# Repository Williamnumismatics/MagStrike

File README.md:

# MagStrike

MagStrike is a custom hall effect keyboard that has a 60 percent layout.
It uses the Gateron Low Profile Magnetic Jade Switches. The brains of this keyboard is a Rpi Pico 2 that runs micropython that communicates with a python script running on the main PC/Laptop

## Why did i build this???
I built this keyboard because i have always wanted to make my own keyboard from scratch and when i stumbled across hall-effect one day i quickly fell in love with it. I also wanted to use low profile switches so my wrists wouldnt hurt all day. I Found the perfect switch for this which is the Gateron Low Profile Magnetic Jade switches.

## What did it take?
It took about 2 weeks to build this it is my first every PCB and unfortunately i couldn't find anywhere to place the rasberry pi pico so i had to put it outside the keyboard. I also designed the case without a top plate so it is easy to print and easy to see the insides

## If i did it again what would i do?
 I would probably make a custom devboard with the rp2040 and embed it inside the footprint of the keyboard.
 
## READ THIS:
the 3d file was to big to commit to github so this is the google drive link:
    https://drive.google.com/file/d/1xGtgr9WMyzFMHPNl8FSLAcrnGV7yFdcr/view
 
### My Bill of Materials

| Item | Description | Quantity | Unit Price (USD) | Total Price (USD) | Shipping(USD) | URL | Running Total(USD) |
| :--- | :--- | :--- | :--- | :--- | :--- | :--- | :--- |
| Switches | Gateron Low Profile Magnetic Jade | 1 x pack of 70 | 56 | 56 | 4.3 | [Link](https://www.gateron.com/products/gateron-low-profile-magnetic-jade-switch?VariantsId=10872) | 60.3 |
| Stabilizer | GATERON Low Profile Plate Mounted Stabilizer | 1 | 8 | 8 | 2.45(Processing Fee) | [Link](https://www.gateron.com/products/gateron-low-profile-plate-mounted-stabilizer?VariantsId=10540) | 70.75 |
| Capacitor | 50V 100nF X7R ±10% 0603 Ceramic Capacitors RoHS | 100 | 0.0025 | 0.25 | 8.87 | [Link](https://www.lcsc.com/product-detail/C14663.html?utm_source=chatgpt.com) | 79.87 |
| Hall Effect Sensor | Analog-Bipolar Hall Effect Sensor | 70 | 0.2345 | 16.42 | N/A | [Link](https://www.lcsc.com/product-detail/C962159.html) | 96.29 |
| Multiplexer | IC MUX 16:1 160OHM 24SOIC | 5 | 0.83 | 3.32 | N/A | [Link](https://www.lcsc.com/sea rch?q=%20CD74HC4067M96%20&s_z=n_%20CD74HC4067M96%20) | 99.61 |
| Rasberry Pi Pico | Rasberry Pi Pico | 1 | 4.32 | 4.32 | 2.42 | [Link](https://core-electronics.com.au/raspberry-pi-pico.html) | 106.35 |
| PCB | THE pcb | 5 | N/A | 26.35 | 18.43 | [Link](https://cart.jlcpcb.com/shopcart/cart/) | 151.13 |

### I didnt include all of the shopping carts so here it is(Note that on gateron website it says some cheaper that the bom but that is cause of a sale that is ending in 16 hours.):

# 3d render:

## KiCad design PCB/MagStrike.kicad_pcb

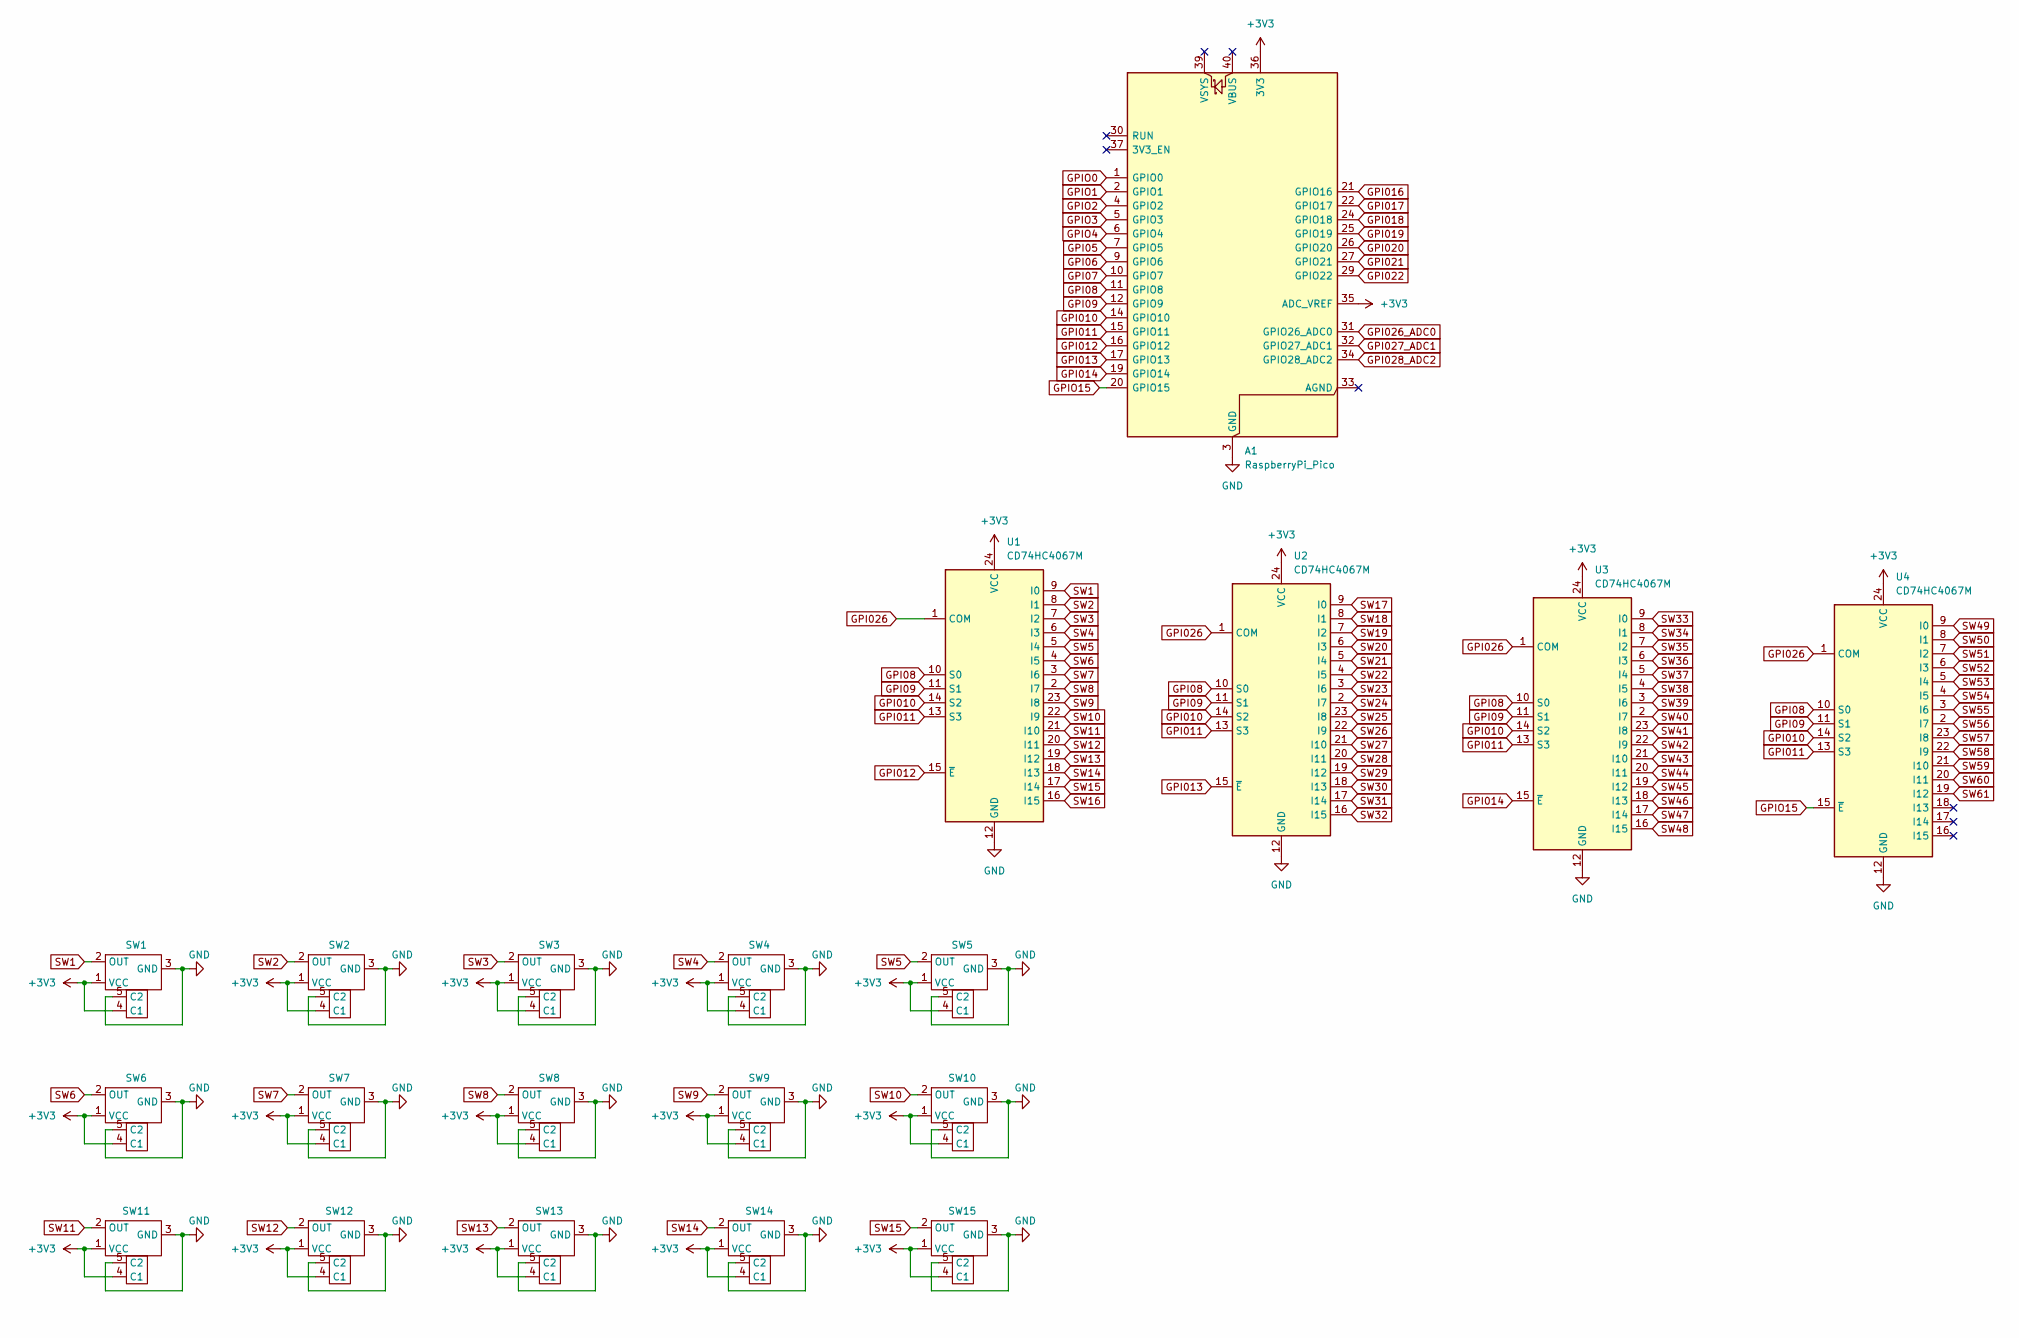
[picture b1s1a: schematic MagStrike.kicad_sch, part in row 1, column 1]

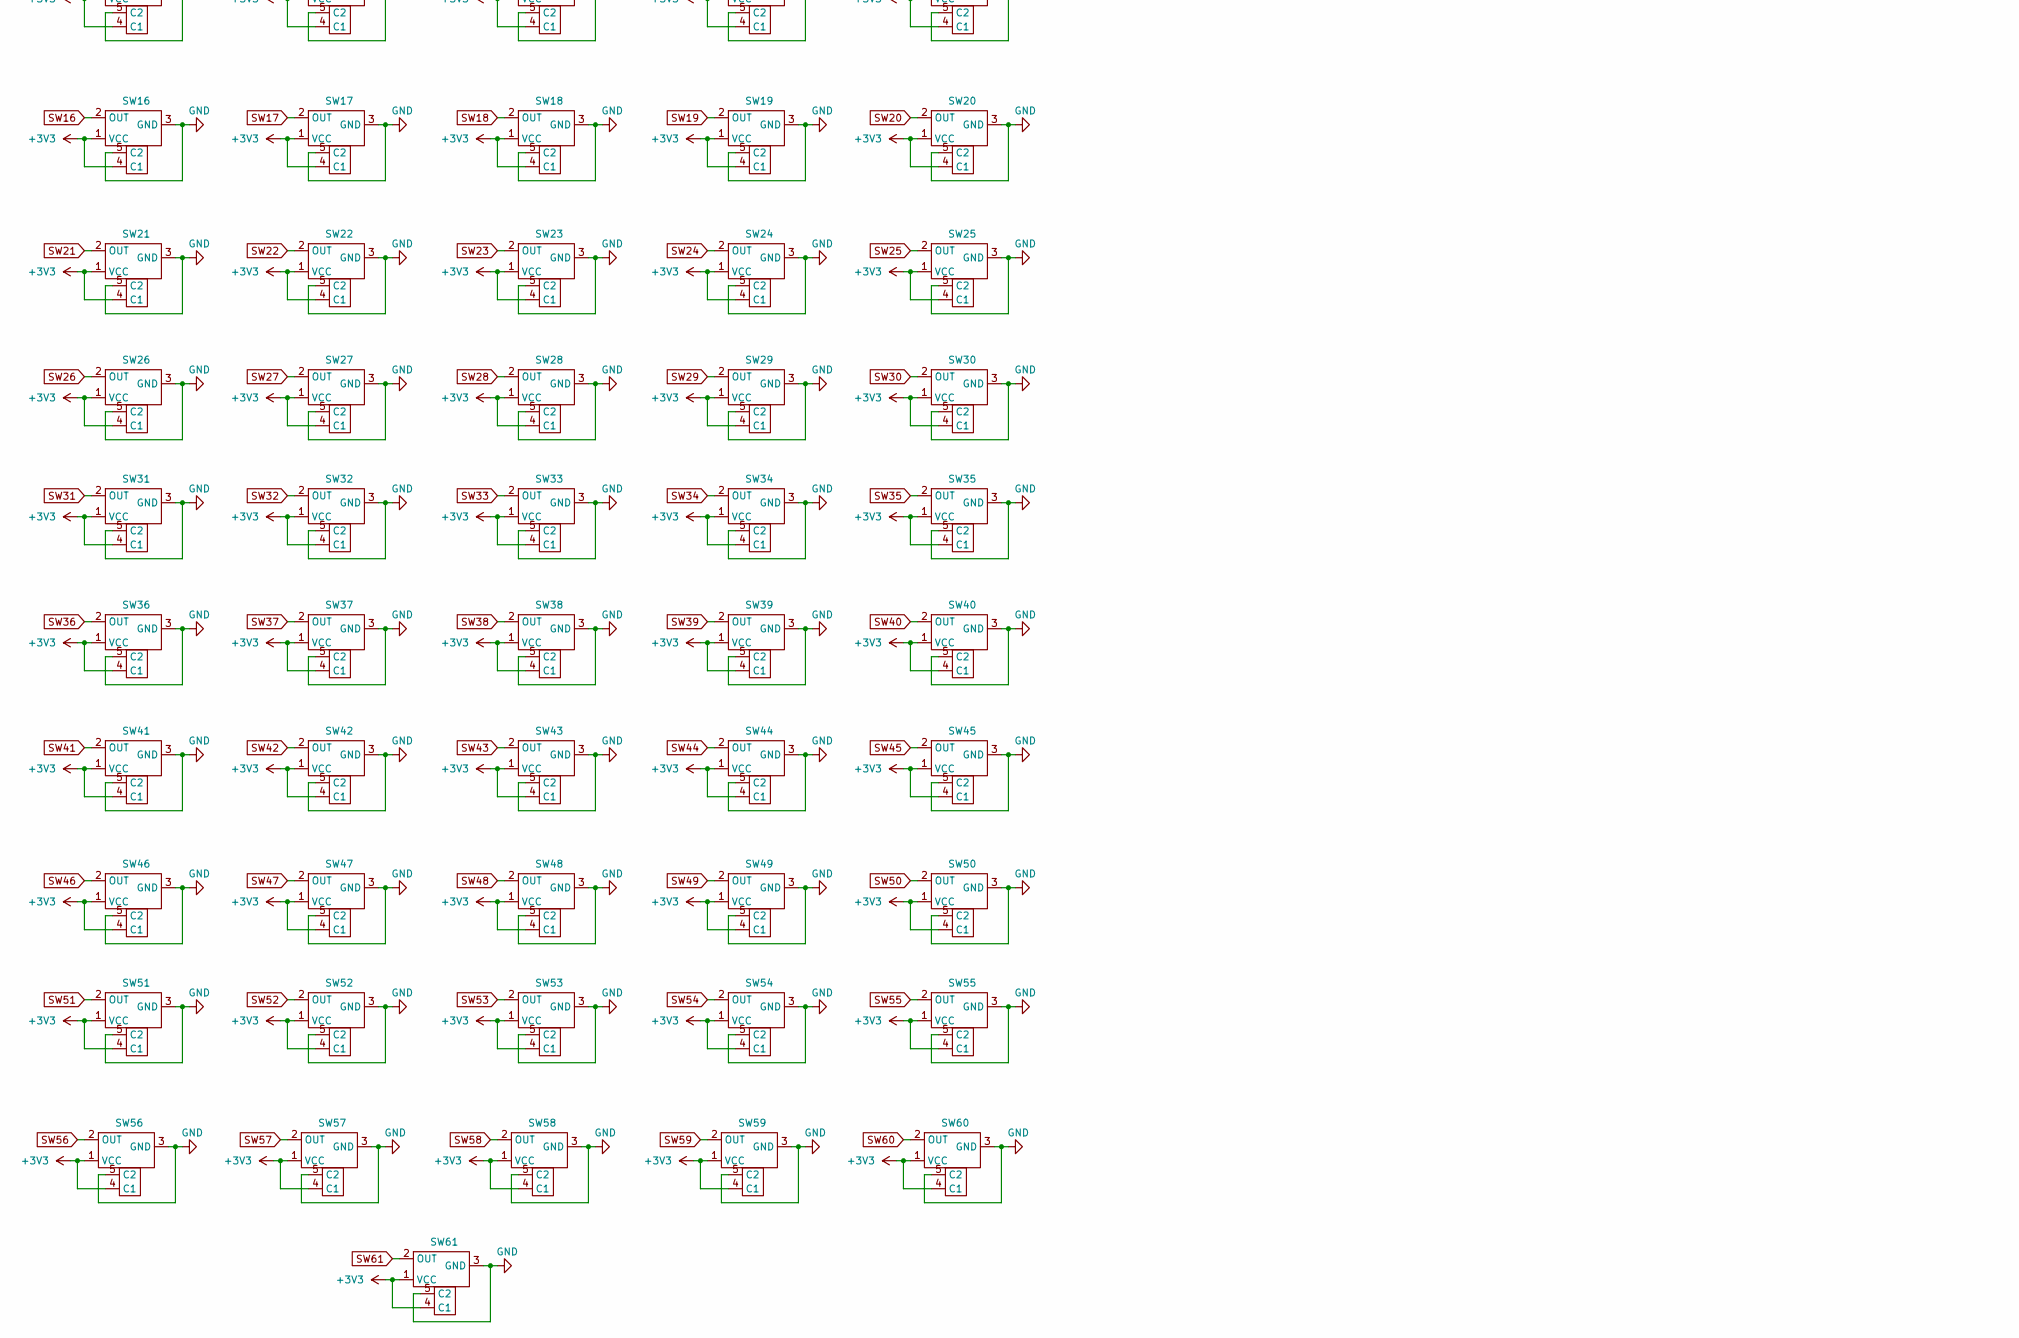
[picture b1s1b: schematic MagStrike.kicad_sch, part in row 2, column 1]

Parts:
A1: RaspberryPi_Pico; RaspberryPi_Pico_Common_Unspecified
SW1, SW2, SW3, SW4, SW5, SW6, SW7, SW8, SW9, SW10, SW11, SW12, SW13, SW14, SW15, SW16, SW17, SW18, SW19, SW20, SW21, SW22, SW23, SW24, SW25, SW26, SW27, SW28, SW29, SW30, SW31, SW32, SW33, SW34, SW35, SW36, SW37, SW38, SW39, SW40, SW41, SW42, SW43, SW44, SW45, SW46, SW47, SW48, SW49, SW50, SW51, SW52, SW53, SW54, SW55, SW56, SW57, SW58, SW59, SW60, SW61: Gateron_Low_Profile_Magnetic_Jade
U1, U2, U3, U4: CD74HC4067M; SOIC-24W_7.5x15.4mm_P1.27mm

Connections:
+3V3: A1.35 (ADC_VREF), A1.36 (3V3), SW1.1 (VCC), SW1.4 (C1), SW2.1 (VCC), SW2.4 (C1), SW3.1 (VCC), SW3.4 (C1), SW4.1 (VCC), SW4.4 (C1), SW5.1 (VCC), SW5.4 (C1), SW6.1 (VCC), SW6.4 (C1), SW7.1 (VCC), SW7.4 (C1), SW8.1 (VCC), SW8.4 (C1), SW9.1 (VCC), SW9.4 (C1), SW10.1 (VCC), SW10.4 (C1), SW11.1 (VCC), SW11.4 (C1), SW12.1 (VCC), SW12.4 (C1), SW13.1 (VCC), SW13.4 (C1), SW14.1 (VCC), SW14.4 (C1), SW15.1 (VCC), SW15.4 (C1), SW16.1 (VCC), SW16.4 (C1), SW17.1 (VCC), SW17.4 (C1), SW18.1 (VCC), SW18.4 (C1), SW19.1 (VCC), SW19.4 (C1), SW20.1 (VCC), SW20.4 (C1), SW21.1 (VCC), SW21.4 (C1), SW22.1 (VCC), SW22.4 (C1), SW23.1 (VCC), SW23.4 (C1), SW24.1 (VCC), SW24.4 (C1), SW25.1 (VCC), SW25.4 (C1), SW26.1 (VCC), SW26.4 (C1), SW27.1 (VCC), SW27.4 (C1), SW28.1 (VCC), SW28.4 (C1), SW29.1 (VCC), SW29.4 (C1), SW30.1 (VCC), SW30.4 (C1), SW31.1 (VCC), SW31.4 (C1), SW32.1 (VCC), SW32.4 (C1), SW33.1 (VCC), SW33.4 (C1), SW34.1 (VCC), SW34.4 (C1), SW35.1 (VCC), SW35.4 (C1), SW36.1 (VCC), SW36.4 (C1), SW37.1 (VCC), SW37.4 (C1), SW38.1 (VCC), SW38.4 (C1), SW39.1 (VCC), SW39.4 (C1), SW40.1 (VCC), SW40.4 (C1), SW41.1 (VCC), SW41.4 (C1), SW42.1 (VCC), SW42.4 (C1), SW43.1 (VCC), SW43.4 (C1), SW44.1 (VCC), SW44.4 (C1), SW45.1 (VCC), SW45.4 (C1), SW46.1 (VCC), SW46.4 (C1), SW47.1 (VCC), SW47.4 (C1), SW48.1 (VCC), SW48.4 (C1), SW49.1 (VCC), SW49.4 (C1), SW50.1 (VCC), SW50.4 (C1), SW51.1 (VCC), SW51.4 (C1), SW52.1 (VCC), SW52.4 (C1), SW53.1 (VCC), SW53.4 (C1), SW54.1 (VCC), SW54.4 (C1), SW55.1 (VCC), SW55.4 (C1), SW56.1 (VCC), SW56.4 (C1), SW57.1 (VCC), SW57.4 (C1), SW58.1 (VCC), SW58.4 (C1), SW59.1 (VCC), SW59.4 (C1), SW60.1 (VCC), SW60.4 (C1), SW61.1 (VCC), SW61.4 (C1), U1.24 (VCC), U2.24 (VCC), U3.24 (VCC), U4.24 (VCC)
GND: A1.3 (GND), A1.8 (GND), A1.13 (GND), A1.18 (GND), A1.23 (GND), A1.28 (GND), A1.38 (GND), SW1.3 (GND), SW1.5 (C2), SW2.3 (GND), SW2.5 (C2), SW3.3 (GND), SW3.5 (C2), SW4.3 (GND), SW4.5 (C2), SW5.3 (GND), SW5.5 (C2), SW6.3 (GND), SW6.5 (C2), SW7.3 (GND), SW7.5 (C2), SW8.3 (GND), SW8.5 (C2), SW9.3 (GND), SW9.5 (C2), SW10.3 (GND), SW10.5 (C2), SW11.3 (GND), SW11.5 (C2), SW12.3 (GND), SW12.5 (C2), SW13.3 (GND), SW13.5 (C2), SW14.3 (GND), SW14.5 (C2), SW15.3 (GND), SW15.5 (C2), SW16.3 (GND), SW16.5 (C2), SW17.3 (GND), SW17.5 (C2), SW18.3 (GND), SW18.5 (C2), SW19.3 (GND), SW19.5 (C2), SW20.3 (GND), SW20.5 (C2), SW21.3 (GND), SW21.5 (C2), SW22.3 (GND), SW22.5 (C2), SW23.3 (GND), SW23.5 (C2), SW24.3 (GND), SW24.5 (C2), SW25.3 (GND), SW25.5 (C2), SW26.3 (GND), SW26.5 (C2), SW27.3 (GND), SW27.5 (C2), SW28.3 (GND), SW28.5 (C2), SW29.3 (GND), SW29.5 (C2), SW30.3 (GND), SW30.5 (C2), SW31.3 (GND), SW31.5 (C2), SW32.3 (GND), SW32.5 (C2), SW33.3 (GND), SW33.5 (C2), SW34.3 (GND), SW34.5 (C2), SW35.3 (GND), SW35.5 (C2), SW36.3 (GND), SW36.5 (C2), SW37.3 (GND), SW37.5 (C2), SW38.3 (GND), SW38.5 (C2), SW39.3 (GND), SW39.5 (C2), SW40.3 (GND), SW40.5 (C2), SW41.3 (GND), SW41.5 (C2), SW42.3 (GND), SW42.5 (C2), SW43.3 (GND), SW43.5 (C2), SW44.3 (GND), SW44.5 (C2), SW45.3 (GND), SW45.5 (C2), SW46.3 (GND), SW46.5 (C2), SW47.3 (GND), SW47.5 (C2), SW48.3 (GND), SW48.5 (C2), SW49.3 (GND), SW49.5 (C2), SW50.3 (GND), SW50.5 (C2), SW51.3 (GND), SW51.5 (C2), SW52.3 (GND), SW52.5 (C2), SW53.3 (GND), SW53.5 (C2), SW54.3 (GND), SW54.5 (C2), SW55.3 (GND), SW55.5 (C2), SW56.3 (GND), SW56.5 (C2), SW57.3 (GND), SW57.5 (C2), SW58.3 (GND), SW58.5 (C2), SW59.3 (GND), SW59.5 (C2), SW60.3 (GND), SW60.5 (C2), SW61.3 (GND), SW61.5 (C2), U1.12 (GND), U2.12 (GND), U3.12 (GND), U4.12 (GND)
GPI05: A1.7 (GPIO5)
GPI06: A1.9 (GPIO6)
GPI07: A1.10 (GPIO7)
GPI08: A1.11 (GPIO8), U1.10 (S0), U2.10 (S0), U3.10 (S0), U4.10 (S0)
GPI09: A1.12 (GPIO9), U1.11 (S1), U2.11 (S1), U3.11 (S1), U4.11 (S1)
GPI010: A1.14 (GPIO10), U1.14 (S2), U2.14 (S2), U3.14 (S2), U4.14 (S2)
GPI011: A1.15 (GPIO11), U1.13 (S3), U2.13 (S3), U3.13 (S3), U4.13 (S3)
GPI012: A1.16 (GPIO12), U1.15 (~E)
GPI013: A1.17 (GPIO13), U2.15 (~E)
GPI014: A1.19 (GPIO14), U3.15 (~E)
GPI016: A1.21 (GPIO16)
GPI017: A1.22 (GPIO17)
GPI018: A1.24 (GPIO18)
GPI019: A1.25 (GPIO19)
GPI020: A1.26 (GPIO20)
GPI021: A1.27 (GPIO21)
GPI022: A1.29 (GPIO22)
GPI026: U1.1 (COM), U2.1 (COM), U3.1 (COM), U4.1 (COM)
GPI026_ADC0: A1.31 (GPIO26_ADC0)
GPI027_ADC1: A1.32 (GPIO27_ADC1)
GPI028_ADC2: A1.34 (GPIO28_ADC2)
GPIO0: A1.1 (GPIO0)
GPIO1: A1.2 (GPIO1)
GPIO2: A1.4 (GPIO2)
GPIO3: A1.5 (GPIO3)
GPIO4: A1.6 (GPIO4)
GPIO15: A1.20 (GPIO15), U4.15 (~E)
SW1: SW1.2 (OUT), U1.9 (I0)
SW2: SW2.2 (OUT), U1.8 (I1)
SW3: SW3.2 (OUT), U1.7 (I2)
SW4: SW4.2 (OUT), U1.6 (I3)
SW5: SW5.2 (OUT), U1.5 (I4)
SW6: SW6.2 (OUT), U1.4 (I5)
SW7: SW7.2 (OUT), U1.3 (I6)
SW8: SW8.2 (OUT), U1.2 (I7)
SW9: SW9.2 (OUT), U1.23 (I8)
SW10: SW10.2 (OUT), U1.22 (I9)
SW11: SW11.2 (OUT), U1.21 (I10)
SW12: SW12.2 (OUT), U1.20 (I11)
SW13: SW13.2 (OUT), U1.19 (I12)
SW14: SW14.2 (OUT), U1.18 (I13)
SW15: SW15.2 (OUT), U1.17 (I14)
SW16: SW16.2 (OUT), U1.16 (I15)
SW17: SW17.2 (OUT), U2.9 (I0)
SW18: SW18.2 (OUT), U2.8 (I1)
SW19: SW19.2 (OUT), U2.7 (I2)
SW20: SW20.2 (OUT), U2.6 (I3)
SW21: SW21.2 (OUT), U2.5 (I4)
SW22: SW22.2 (OUT), U2.4 (I5)
SW23: SW23.2 (OUT), U2.3 (I6)
SW24: SW24.2 (OUT), U2.2 (I7)
SW25: SW25.2 (OUT), U2.23 (I8)
SW26: SW26.2 (OUT), U2.22 (I9)
SW27: SW27.2 (OUT), U2.21 (I10)
SW28: SW28.2 (OUT), U2.20 (I11)
SW29: SW29.2 (OUT), U2.19 (I12)
SW30: SW30.2 (OUT), U2.18 (I13)
SW31: SW31.2 (OUT), U2.17 (I14)
SW32: SW32.2 (OUT), U2.16 (I15)
SW33: SW33.2 (OUT), U3.9 (I0)
SW34: SW34.2 (OUT), U3.8 (I1)
SW35: SW35.2 (OUT), U3.7 (I2)
SW36: SW36.2 (OUT), U3.6 (I3)
SW37: SW37.2 (OUT), U3.5 (I4)
SW38: SW38.2 (OUT), U3.4 (I5)
SW39: SW39.2 (OUT), U3.3 (I6)
SW40: SW40.2 (OUT), U3.2 (I7)
SW41: SW41.2 (OUT), U3.23 (I8)
SW42: SW42.2 (OUT), U3.22 (I9)
SW43: SW43.2 (OUT), U3.21 (I10)
SW44: SW44.2 (OUT), U3.20 (I11)
SW45: SW45.2 (OUT), U3.19 (I12)
SW46: SW46.2 (OUT), U3.18 (I13)
SW47: SW47.2 (OUT), U3.17 (I14)
SW48: SW48.2 (OUT), U3.16 (I15)
SW49: SW49.2 (OUT), U4.9 (I0)
SW50: SW50.2 (OUT), U4.8 (I1)
SW51: SW51.2 (OUT), U4.7 (I2)
SW52: SW52.2 (OUT), U4.6 (I3)
SW53: SW53.2 (OUT), U4.5 (I4)
SW54: SW54.2 (OUT), U4.4 (I5)
SW55: SW55.2 (OUT), U4.3 (I6)
SW56: SW56.2 (OUT), U4.2 (I7)
SW57: SW57.2 (OUT), U4.23 (I8)
SW58: SW58.2 (OUT), U4.22 (I9)
SW59: SW59.2 (OUT), U4.21 (I10)
SW60: SW60.2 (OUT), U4.20 (I11)
SW61: SW61.2 (OUT), U4.19 (I12)

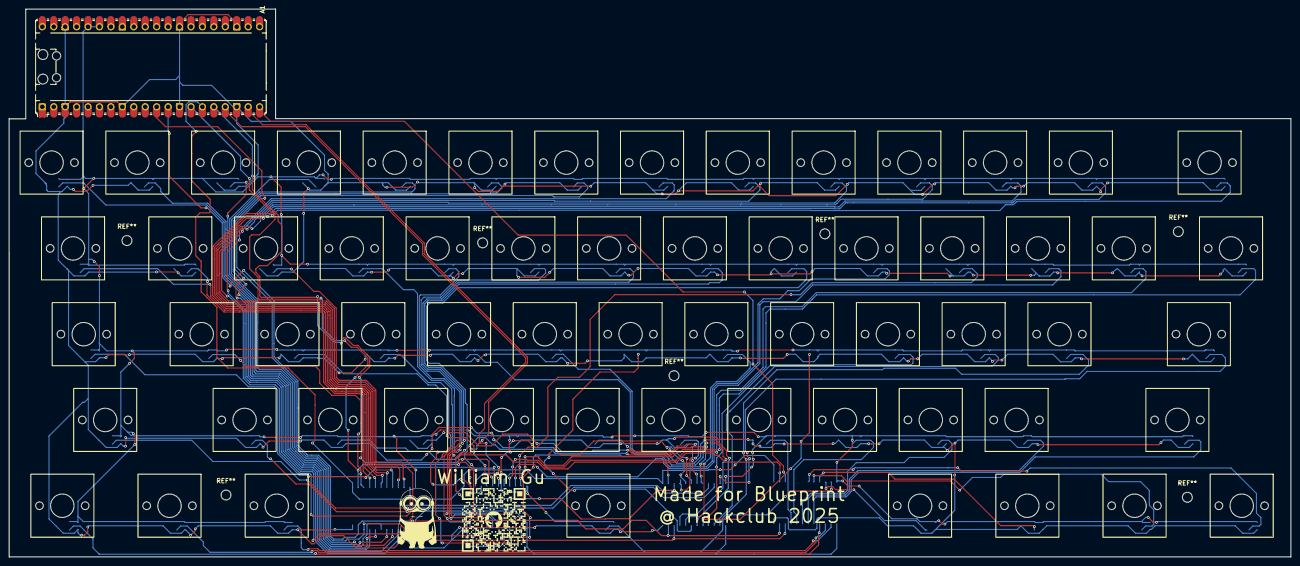
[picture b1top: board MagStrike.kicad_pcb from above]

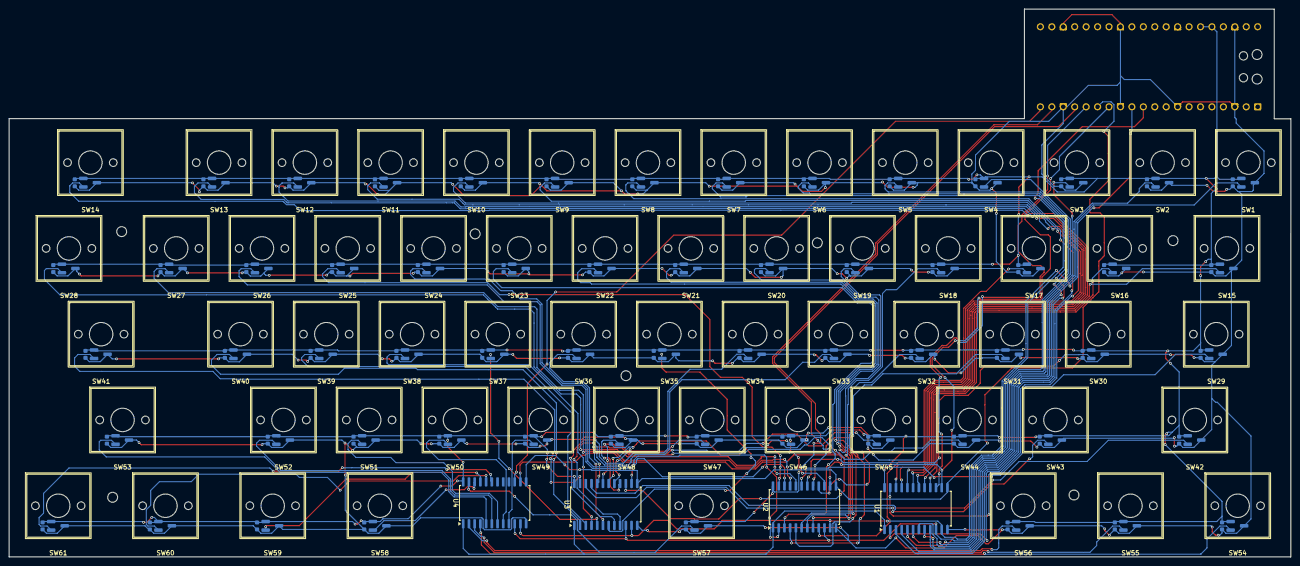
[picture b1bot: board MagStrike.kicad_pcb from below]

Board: 2 copper layers, 284.7 x 121.7 mm, 66 parts (65 on the bottom side), 72 nets.

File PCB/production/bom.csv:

Designator,Footprint,Quantity,Value,LCSC Part #
A1,RaspberryPi_Pico_Common_Unspecified,1,RaspberryPi_Pico,
"SW1, SW10, SW11, SW12, SW13, SW14, SW15, SW16, SW17, SW18, SW19, SW2, SW20, SW21, SW22, SW23, SW24, SW25, SW26, SW27, SW28, SW29, SW3, SW30, SW31, SW32, SW33, SW34, SW35, SW36, SW37, SW38, SW39, SW4, SW40, SW41, SW42, SW43, SW44, SW45, SW46, SW47, SW48, SW49, SW5, SW50, SW51, SW52, SW53, SW54, SW55, SW56, SW57, SW58, SW59, SW6, SW60, SW61, SW7, SW8, SW9",Gateron_Low_Profile_Magnetic_Jade,61,~,
"U1, U2, U3, U4",SOIC-24W_7.5x15.4mm_P1.27mm,4,CD74HC4067M,

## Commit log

2025-10-23 Created files
    Created BOM and Plan files
2025-10-23 started on plan
2025-10-23 Created PCB files
2025-10-23 added lots of kicad stuff
2025-10-24 added stuff
2025-10-30 more stuff
2025-10-31 a
    Former-commit-id: 5bc5bd5ef2ed26bd0dc48ccef968d0766c1999c1
2025-10-31 a
    Former-commit-id: a0e78644dac945afff92ae1704eef0a00ba53631
2025-11-01 more
2025-11-02 Create .README.md.kate-swp
2025-11-09 sad
    me is dum i just figured out that in the specs my switch requres the sensor to be on the borrom and i put them in the top welp ima gonna start the pcb over :(
2025-11-09 aaa
    more stuff
2025-11-10 t
    f
2025-11-10 alnm sdklnsdjklsdf
    more traces 👍
2025-11-11 more traces
    more traces
2025-11-11 yieee
    finished hopefully
2025-11-12 finilization
    I hope this is the final one
2025-11-12 more
    stuff just silkscreen now tho
2025-11-12 mr
    r
2025-11-12 more refining
    more refining
2025-11-13 more stuff
    more silkscreening
2025-11-13 fixed drc issues
2025-11-30 stuff
2025-12-01 some sad things
    i have my pcb but relised i have done the pinout wrong
2025-12-04 more stuff
    mores stutff
2025-12-08 push final 1.2
    This is the mabe final version for my thing it should be done i will do some final checks tho
2025-12-08 added my plan Link
2025-12-08 final stuff with silkscreen
2025-12-09 idk what i did
2025-12-09 tests
2025-12-09 added a step file
